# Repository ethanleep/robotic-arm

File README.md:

# Scorebot-ER III
This is my repo for the custom controller I've been designing and assembling for the Scorebot-ER III.
All files here are to be considered a work in progress as they are far from perfect.

The main serial controlled code is robotic_arm_main.ino while the main hard coded code is Custom_movement.ino

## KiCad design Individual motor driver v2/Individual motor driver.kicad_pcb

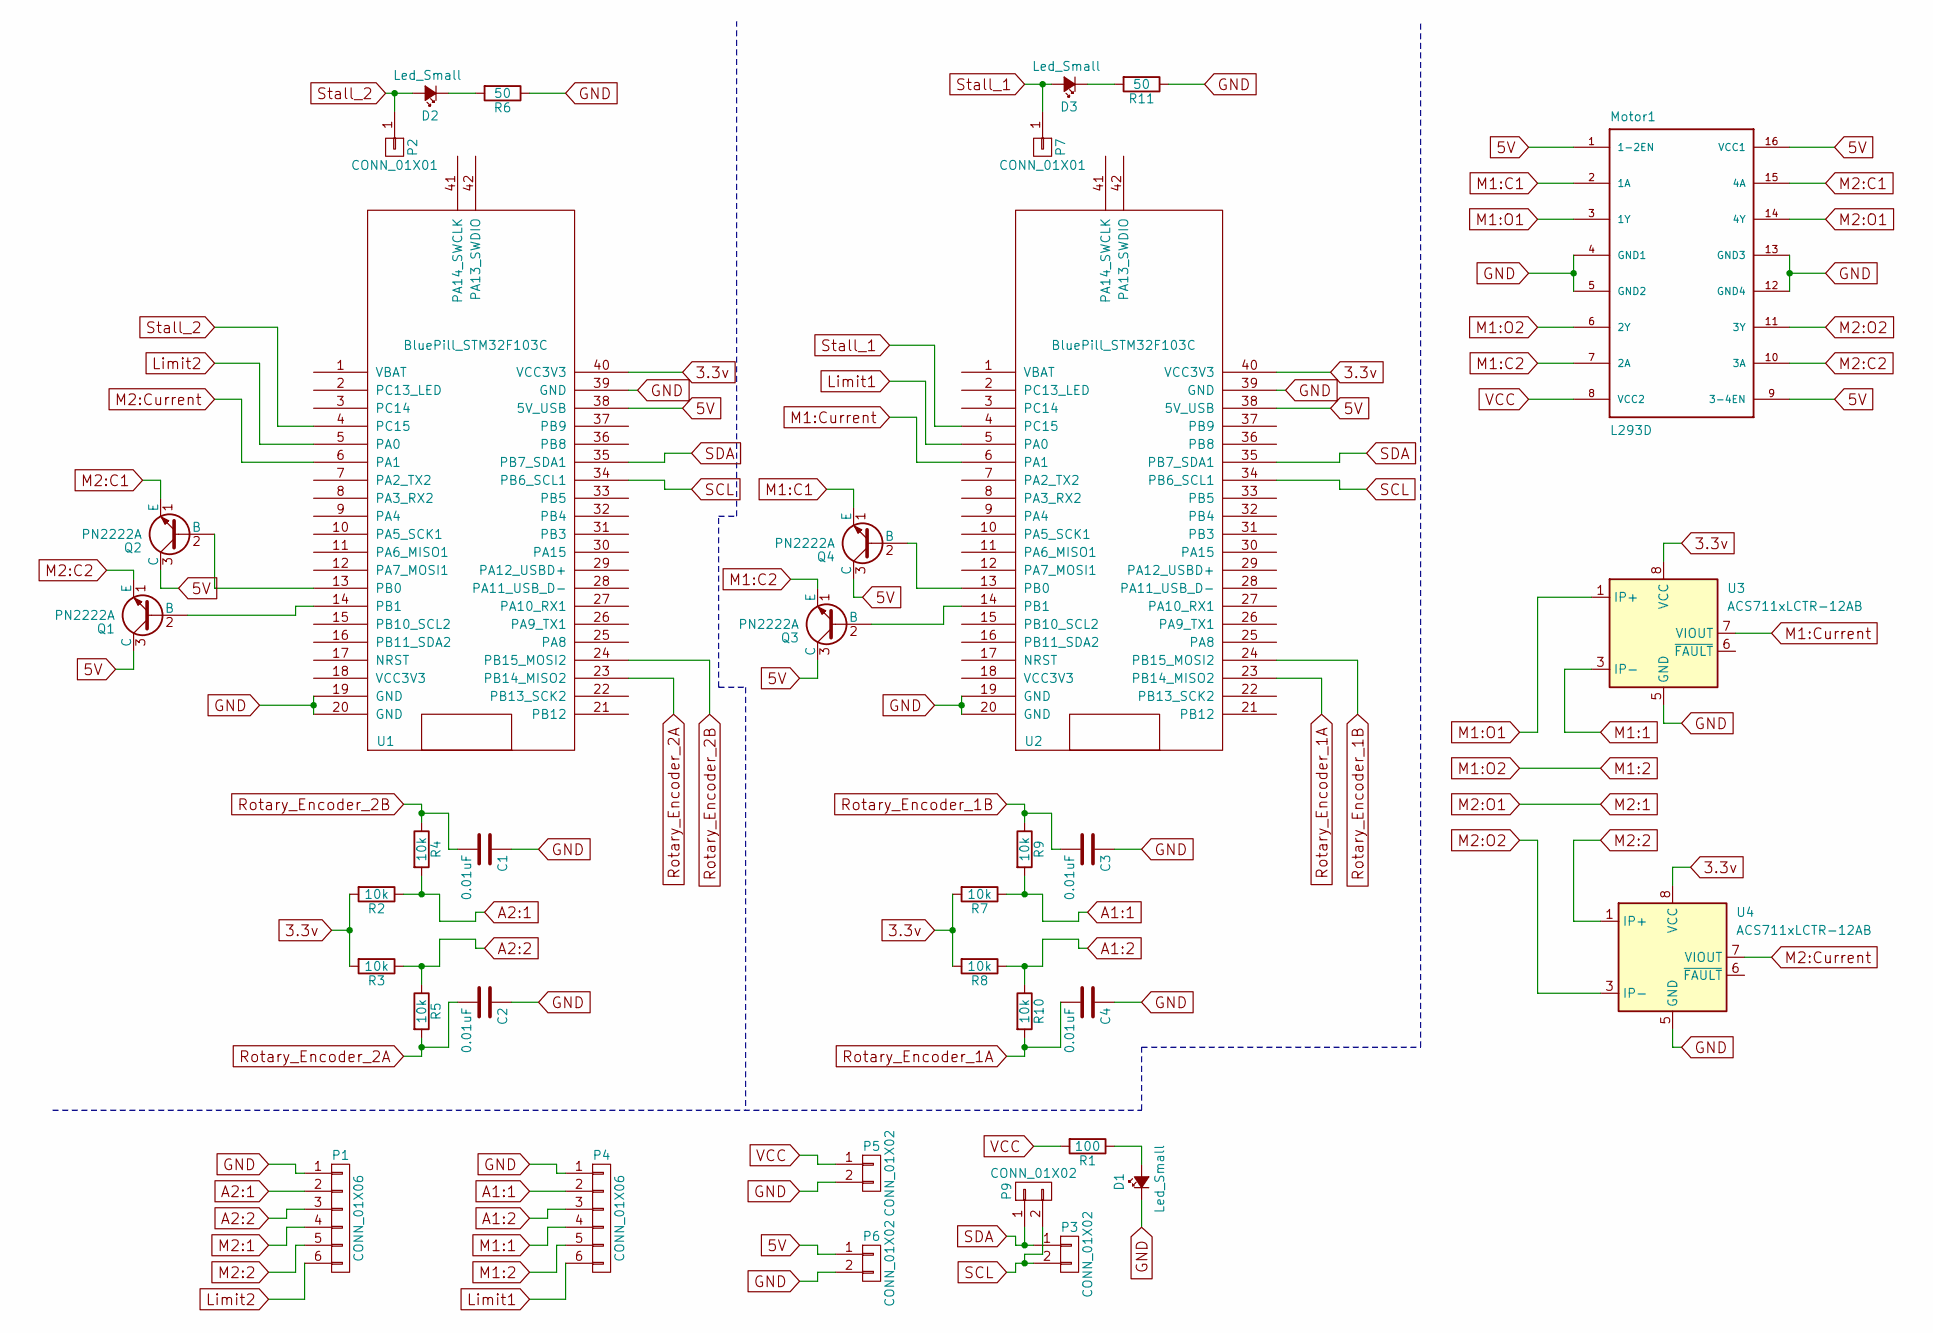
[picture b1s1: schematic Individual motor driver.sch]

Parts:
C1, C2, C3, C4: 0.01uF; C_Axial_L3.8mm_D2.6mm_P7.50mm_Horizontal
D1, D2, D3: Led_Small; LED_D3.0mm
Motor1: L293D; DIP-16_W7.62mm
P1, P4: CONN_01X06; PinHeader_1x06_P2.54mm_Horizontal
P2, P7: CONN_01X01; PinHeader_1x01_P2.54mm_Vertical
P3, P5, P6, P9: CONN_01X02; PinHeader_1x02_P2.54mm_Vertical
Q1, Q2, Q3, Q4: PN2222A; TO-92_Inline
R1: 100; R_Axial_DIN0207_L6.3mm_D2.5mm_P10.16mm_Horizontal
R2, R3, R4, R5, R7, R8, R9, R10: 10k; R_Axial_DIN0207_L6.3mm_D2.5mm_P10.16mm_Horizontal
R6, R11: 50; R_Axial_DIN0207_L6.3mm_D2.5mm_P10.16mm_Horizontal
U1, U2: BluePill_STM32F103C
U3, U4: ACS711xLCTR-12AB; SOIC-8_3.9x4.9mm_P1.27mm

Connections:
3.3v: R2.2, R3.2, R7.2, R8.2, U1.40 (VCC3V3), U2.40 (VCC3V3), U3.8 (VCC), U4.8 (VCC)
5V: Motor1.1 (1-2EN), Motor1.9 (3-4EN), Motor1.16 (VCC1), P6.1, Q1.3 (C), Q2.3 (C), Q3.3 (C), Q4.3 (C), U1.38 (5V_USB), U2.38 (5V_USB)
A1:1: P4.2, R7.1, R9.2
A1:2: P4.3, R8.1, R10.1
A2:1: P1.2, R2.1, R4.2
A2:2: P1.3, R3.1, R5.1
GND: C1.1, C2.1, C3.1, C4.1, D1.1 (K), Motor1.4 (GND1), Motor1.5 (GND2), Motor1.12 (GND4), Motor1.13 (GND3), P1.1, P4.1, P5.2, P6.2, R6.1, R11.1, U1.19 (GND), U1.20 (GND), U1.39 (GND), U2.19 (GND), U2.20 (GND), U2.39 (GND), U3.5 (GND), U4.5 (GND)
Limit1: P4.6, U2.5 (PA0)
Limit2: P1.6, U1.5 (PA0)
M1:1: P4.4, U3.3 (IP-), U3.4 (IP-); also elsewhere on the board
M1:2: Motor1.6 (2Y), P4.5
M1:C1: Motor1.2 (1A), Q4.1 (E)
M1:C2: Motor1.7 (2A), Q3.1 (E)
M1:Current: U2.6 (PA1), U3.7 (VIOUT)
M1:O1: Motor1.3 (1Y), U3.1 (IP+), U3.2 (IP+); also elsewhere on the board
M2:1: Motor1.14 (4Y), P1.4
M2:2: P1.5, U4.1 (IP+), U4.2 (IP+); also elsewhere on the board
M2:C1: Motor1.15 (4A), Q2.1 (E)
M2:C2: Motor1.10 (3A), Q1.1 (E)
M2:Current: U1.6 (PA1), U4.7 (VIOUT)
M2:O2: Motor1.11 (3Y), U4.3 (IP-), U4.4 (IP-); also elsewhere on the board
unnamed: D1.2 (A), R1.1
unnamed: D2.1 (K), R6.2
unnamed: D3.1 (K), R11.2
unnamed: Q1.2 (B), U1.14 (PB1)
unnamed: Q2.2 (B), U1.13 (PB0)
unnamed: Q3.2 (B), U2.14 (PB1)
unnamed: Q4.2 (B), U2.13 (PB0)
Rotary_Encoder_1A: C4.2, R10.2, U2.23 (PB14_MISO2)
Rotary_Encoder_1B: C3.2, R9.1, U2.24 (PB15_MOSI2)
Rotary_Encoder_2A: C2.2, R5.2, U1.23 (PB14_MISO2)
Rotary_Encoder_2B: C1.2, R4.1, U1.24 (PB15_MOSI2)
SCL: P3.2, P9.2, U1.34 (PB6_SCL1), U2.34 (PB6_SCL1)
SDA: P3.1, P9.1, U1.35 (PB7_SDA1), U2.35 (PB7_SDA1)
Stall_1: D3.2 (A), P7.1, U2.4 (PC15)
Stall_2: D2.2 (A), P2.1, U1.4 (PC15)
VCC: Motor1.8 (VCC2), P5.1, R1.2

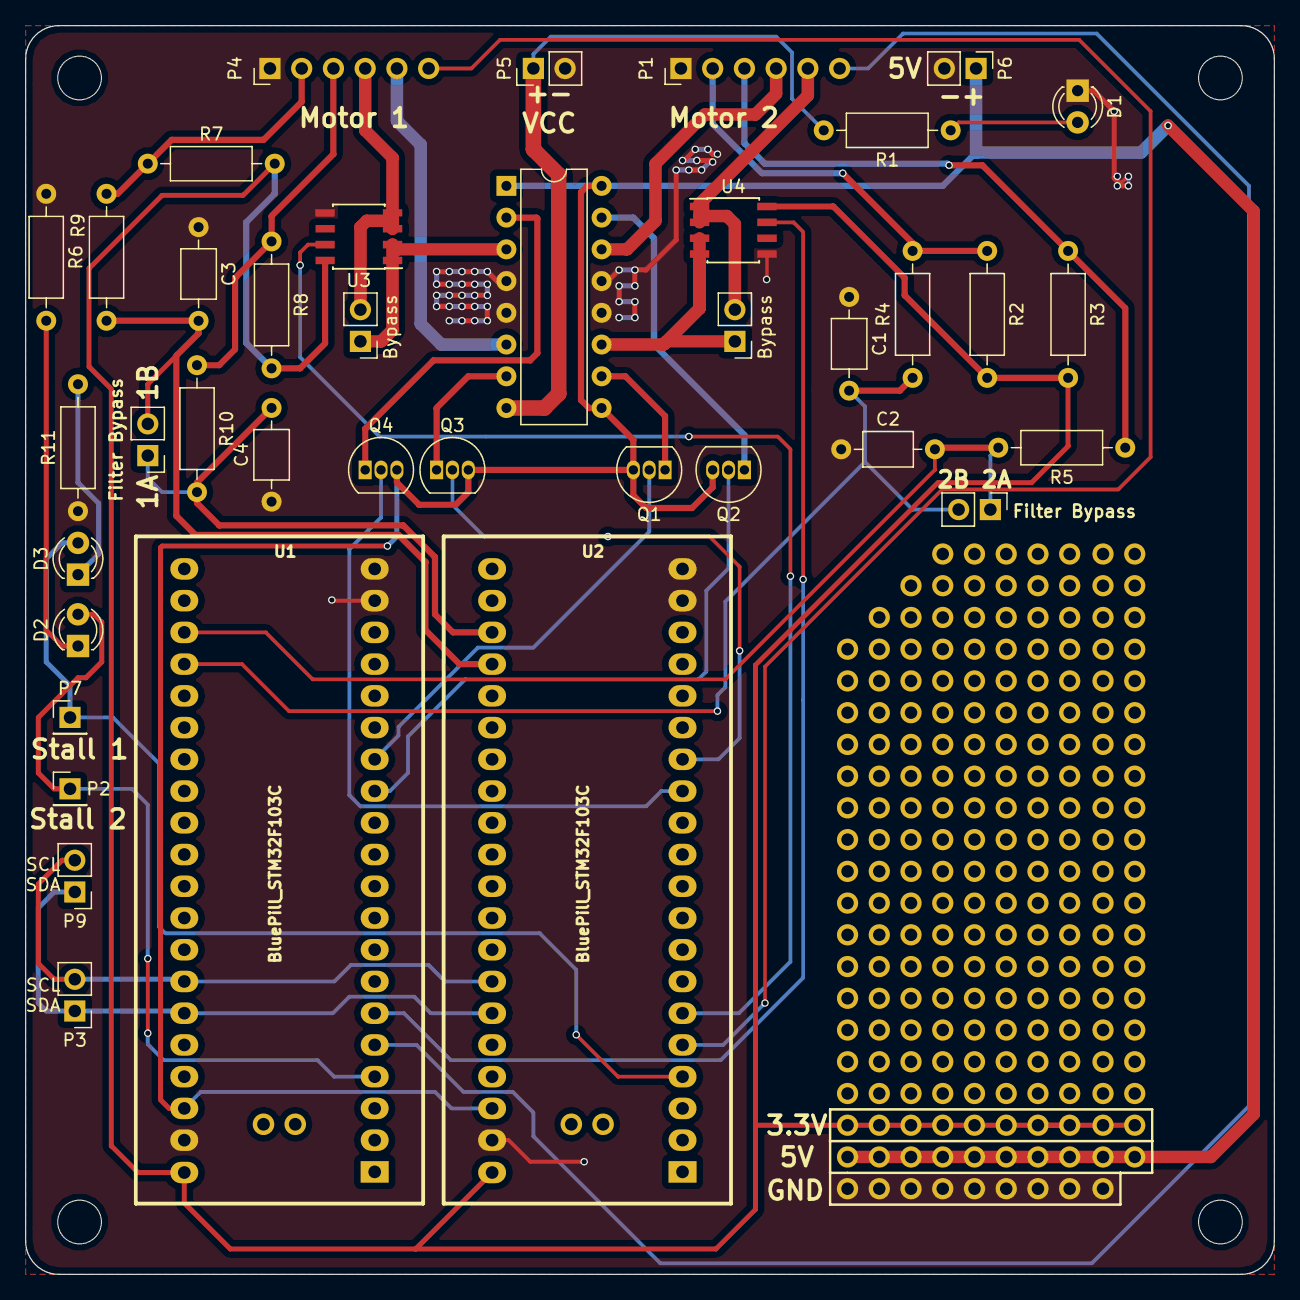
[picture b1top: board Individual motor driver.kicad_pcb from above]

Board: 2 copper layers, 99.9 x 99.9 mm, 37 parts (0 on the bottom side), 37 nets.

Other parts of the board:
Bypass: PinHeader_1x02_P2.54mm_Vertical
Bypass#2: PinHeader_1x02_P2.54mm_Vertical

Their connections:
M1:1: Bypass.2; also elsewhere on the board
M1:O1: Bypass.1; also elsewhere on the board
M2:2: Bypass#2.2; also elsewhere on the board
M2:O2: Bypass#2.1; also elsewhere on the board

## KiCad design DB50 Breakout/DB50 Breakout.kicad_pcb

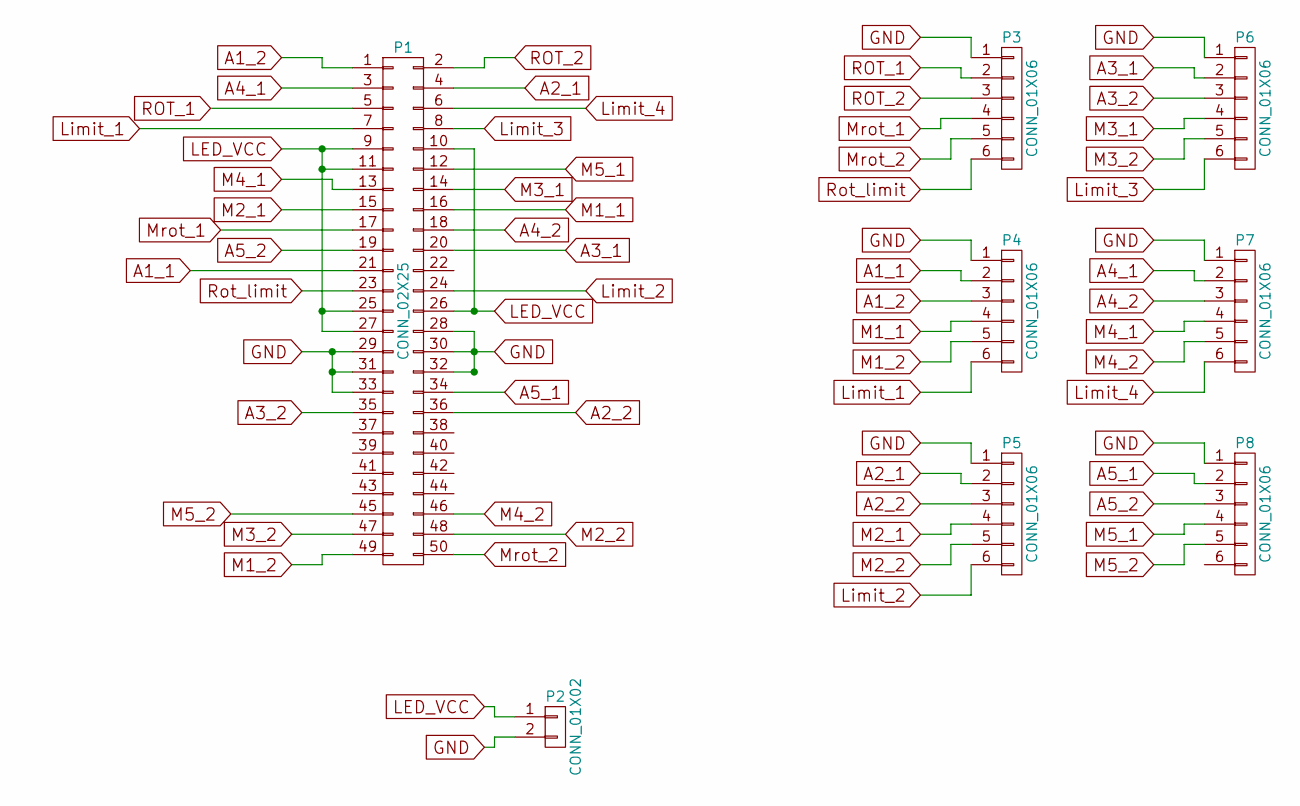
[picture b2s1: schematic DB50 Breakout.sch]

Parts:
P1: CONN_02X25; Dsub_50
P2: CONN_01X02; PinHeader_1x02_P2.54mm_Vertical
P3, P4, P5, P6, P7, P8: CONN_01X06; PinHeader_1x06_P2.54mm_Vertical

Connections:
A1_1: P1.21, P4.2
A1_2: P1.1, P4.3
A2_1: P1.4, P5.2
A2_2: P1.36, P5.3
A3_1: P1.20, P6.2
A3_2: P1.35, P6.3
A4_1: P1.3, P7.2
A4_2: P1.18, P7.3
A5_1: P1.34, P8.2
A5_2: P1.19, P8.3
GND: P1.28, P1.29, P1.30, P1.31, P1.32, P1.33, P2.2, P3.1, P4.1, P5.1, P6.1, P7.1, P8.1
LED_VCC: P1.9, P1.10, P1.11, P1.25, P1.26, P1.27, P2.1
Limit_1: P1.7, P4.6
Limit_2: P1.24, P5.6
Limit_3: P1.8, P6.6
Limit_4: P1.6, P7.6
M1_1: P1.16, P4.4
M1_2: P1.49, P4.5
M2_1: P1.15, P5.4
M2_2: P1.48, P5.5
M3_1: P1.14, P6.4
M3_2: P1.47, P6.5
M4_1: P1.13, P7.4
M4_2: P1.46, P7.5
M5_1: P1.12, P8.4
M5_2: P1.45, P8.5
Mrot_1: P1.17, P3.4
Mrot_2: P1.50, P3.5
ROT_1: P1.5, P3.2
ROT_2: P1.2, P3.3
Rot_limit: P1.23, P3.6

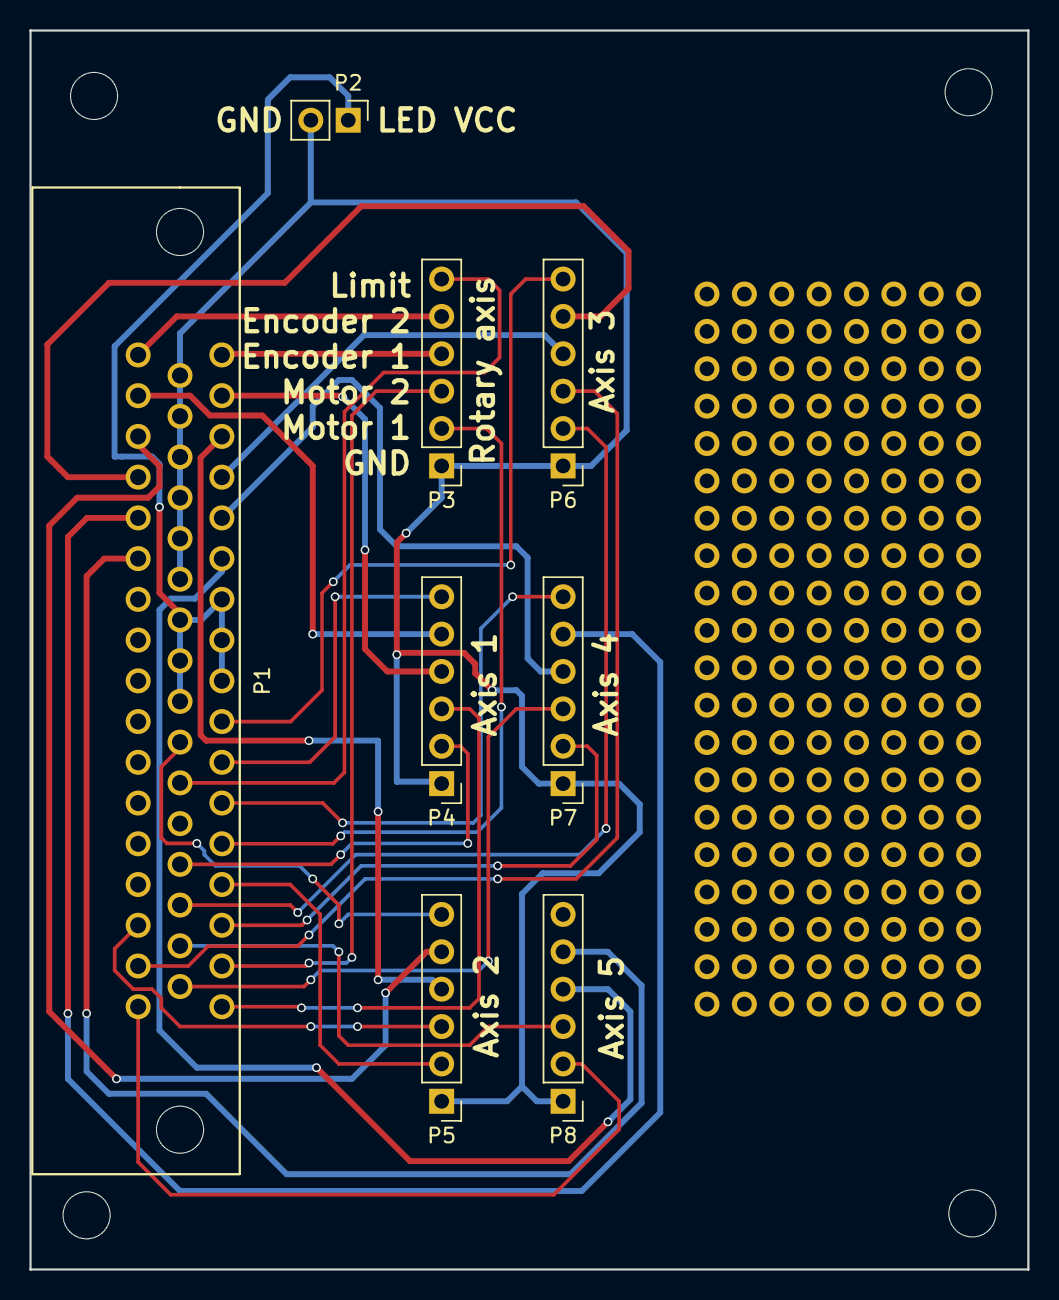
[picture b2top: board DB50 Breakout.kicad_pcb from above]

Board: 2 copper layers, 67.8 x 84.2 mm, 8 parts (0 on the bottom side), 31 nets.

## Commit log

2018-10-30 Rename robot_arm_with_encoder.ino to robot_arm_main.ino
2018-10-30 Added Controller Housing files
2018-10-30 Updated description
2018-10-31 Added PCB files O
2018-11-01 New controller
2018-11-01 Added license
2018-11-04 Added descriptions on the custom movement code
2018-11-05 Further work on the new controller PCB
2018-11-06 PCB file update
2018-11-06 Updated files
2018-11-14 New PCB project
2018-11-14 Update files
2018-11-15 Finished routing and improved some design flaws
2018-11-15 PCB updates
2018-11-16 Misc. Changes to PCB
2018-11-20 Fixed rotary encoder filter
2018-11-29 Added DB50 breakout schematic
2018-11-30 Started routing on DB50 breakout
2018-12-03 Updated DB50 breakout
2018-12-05 New version of board file
2018-12-06 Continued routing on board
2018-12-06 Finished routing and added silkscreen
2018-12-06 Updated V2 files
2018-12-07 Updated DB50 breakout size
2018-12-10 Updated breakout
2018-12-11 Added dimensions and gerber files
2018-12-13 Made small changes to the V2 board and regenerated gerbers
2018-12-13 Forgot to save files before uploading
2019-01-21 Started on STM32 master/slave code
2019-01-25 Updated STM32 slave and master code
2019-02-08 Updated master and slave code
2019-06-18 Added a PDF of the manual for the project
2019-10-29 Made serial communication faster
